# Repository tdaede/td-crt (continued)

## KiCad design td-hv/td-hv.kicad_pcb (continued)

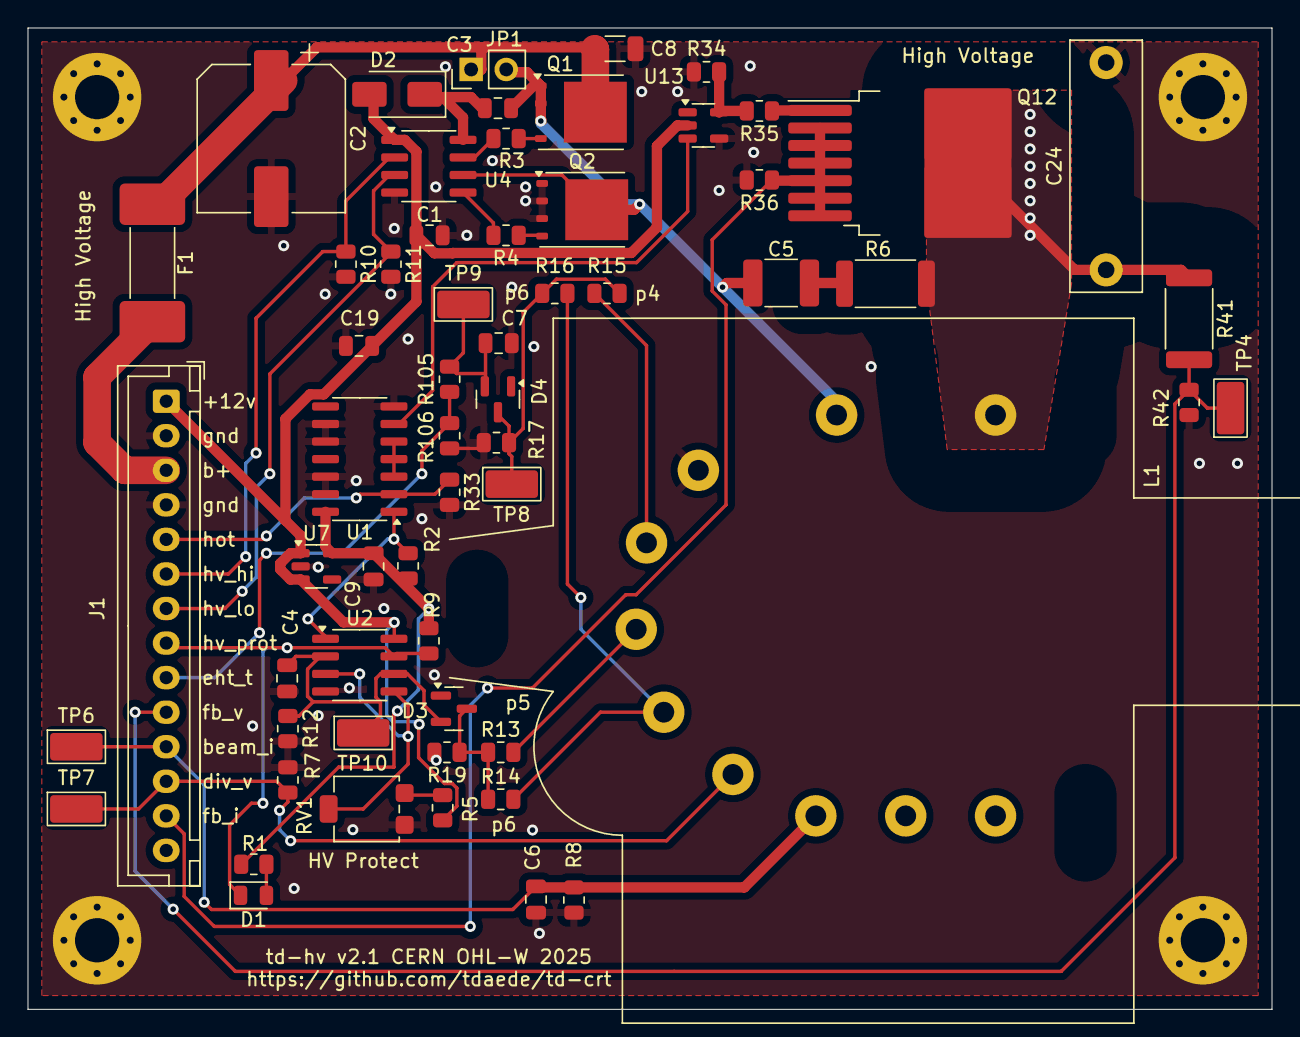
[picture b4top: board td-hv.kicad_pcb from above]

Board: 2 copper layers, 90.0 x 71.0 mm, 64 parts (0 on the bottom side), 37 nets.

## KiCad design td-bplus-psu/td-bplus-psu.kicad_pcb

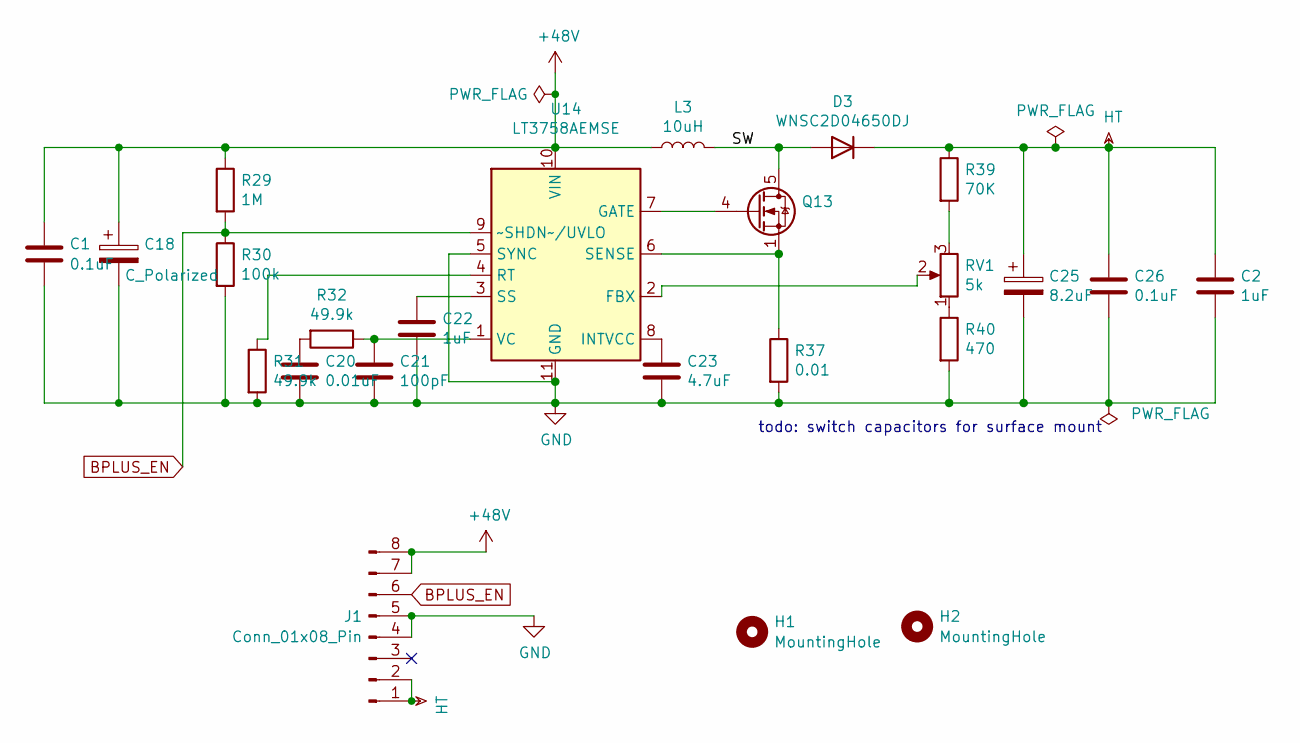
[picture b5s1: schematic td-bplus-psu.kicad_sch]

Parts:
C1: 0.1uF; C_0805_2012Metric; Digikey 399-C0805C104M5RAC7800CT-ND
C2: 1uF; C_2220_5750Metric_Pad1.97x5.40mm_HandSolder; Voltage 250V; Digikey 490-13318-1-ND
C18: C_Polarized; CP_Elec_6.3x5.9; Voltage 63V; Digikey P15466CT-ND
C20: 0.01uF; C_0805_2012Metric_Pad1.18x1.45mm_HandSolder; Voltage 10V; Digikey 1276-2434-1-ND
C21: 100pF; C_0805_2012Metric_Pad1.18x1.45mm_HandSolder; Voltage 10V; Digikey 1276-2569-1-ND
C22: 1uF; C_0805_2012Metric; Voltage 10V; Digikey 587-2229-1-ND
C23: 4.7uF; C_0805_2012Metric_Pad1.18x1.45mm_HandSolder; Voltage 10V; Digikey 1276-3177-1-ND
C25: 8.2uF; CP_Radial_D10.0mm_P5.00mm; Voltage 250V; Digikey 399-14135-ND
C26: 0.1uF; C_1206_3216Metric_Pad1.33x1.80mm_HandSolder; Voltage 250V; Digikey 311-4585-1-ND
D3: WNSC2D04650DJ; TO-252-2_TabPin1; Digikey 1740-WNSC2D04650DJCT-ND
H1, H2: MountingHole; MountingHole_2.7mm_M2.5
J1: Conn_01x08_Pin; PinHeader_1x08_P2.54mm_Horizontal
L3: 10uH; L_Wuerth_HCI-1040; Digikey 732-4179-1-ND
Q13: TDSON-8-1
R29: 1M; R_0805_2012Metric_Pad1.20x1.40mm_HandSolder; Digikey 311-1.00MCRCT-ND
R30: 100k; R_0805_2012Metric_Pad1.20x1.40mm_HandSolder; Digikey 311-100KCRCT-ND
R31, R32: 49.9k; R_0805_2012Metric_Pad1.20x1.40mm_HandSolder; Digikey 311-49.9KCRCT-ND
R37: 0.01; R_0805_2012Metric_Pad1.20x1.40mm_HandSolder; Digikey 311-0.01NUCT-ND
R39: 70K; R_1206_3216Metric_Pad1.30x1.75mm_HandSolder; Digikey 311-68.0KFRCT-ND
R40: 470; R_0805_2012Metric_Pad1.20x1.40mm_HandSolder; Digikey 311-470CRCT-ND
RV1: 5k; Potentiometer_Bourns_3314S_Horizontal; Digikey 3314S-1-502ECT-ND
U14: LT3758AEMSE; MSOP-10-1EP_3x3mm_P0.5mm_EP1.68x1.88mm; Digikey LT3758AEMSE#TRPBFCT-ND

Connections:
+48V: C1.1, C18.1, J1.7, J1.8, L3.1, R29.1, U14.10 (VIN)
/SW: D3.2 (A), L3.2, Q13.5 (D)
BPLUS_EN: J1.6, R29.2, R30.1, U14.9 (~SHDN~/UVLO)
GND: C1.2, C2.2, C18.2, C20.2, C21.2, C22.2, C23.2, C25.2, C26.2, J1.4, J1.5, R30.2, R31.2, R37.2, R40.2, U14.5 (SYNC), U14.11 (GND)
HT: C2.1, C25.1, C26.1, D3.1 (K), J1.1, J1.2, R39.1
unnamed: C20.1, R32.2
unnamed: Q13.4 (G), U14.7 (GATE)
unnamed: R39.2, RV1.3
unnamed: R40.1, RV1.1
unnamed: RV1.2, U14.2 (FBX)
unnamed: C23.1, U14.8 (INTVCC)
unnamed: R31.1, U14.4 (RT)
unnamed: Q13.1 (S), Q13.2 (S), Q13.3 (S), R37.1, U14.6 (SENSE)
unnamed: C22.1, U14.3 (SS)
unnamed: C21.1, R32.1, U14.1 (VC)

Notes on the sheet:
todo: switch capacitors for surface mount

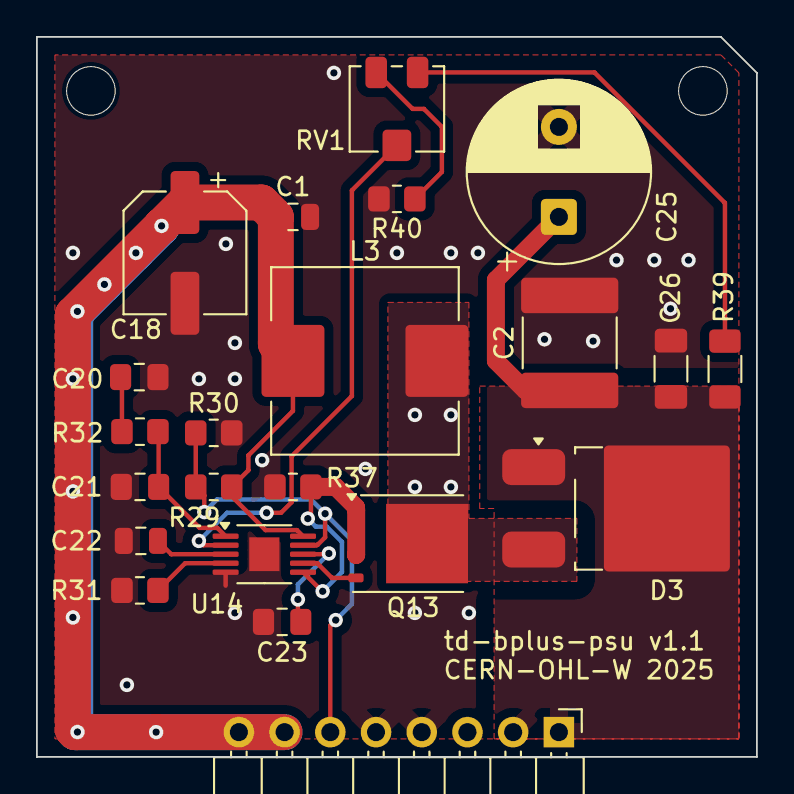
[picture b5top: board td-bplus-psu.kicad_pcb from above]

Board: 2 copper layers, 40.0 x 40.0 mm, 24 parts (0 on the bottom side), 15 nets.

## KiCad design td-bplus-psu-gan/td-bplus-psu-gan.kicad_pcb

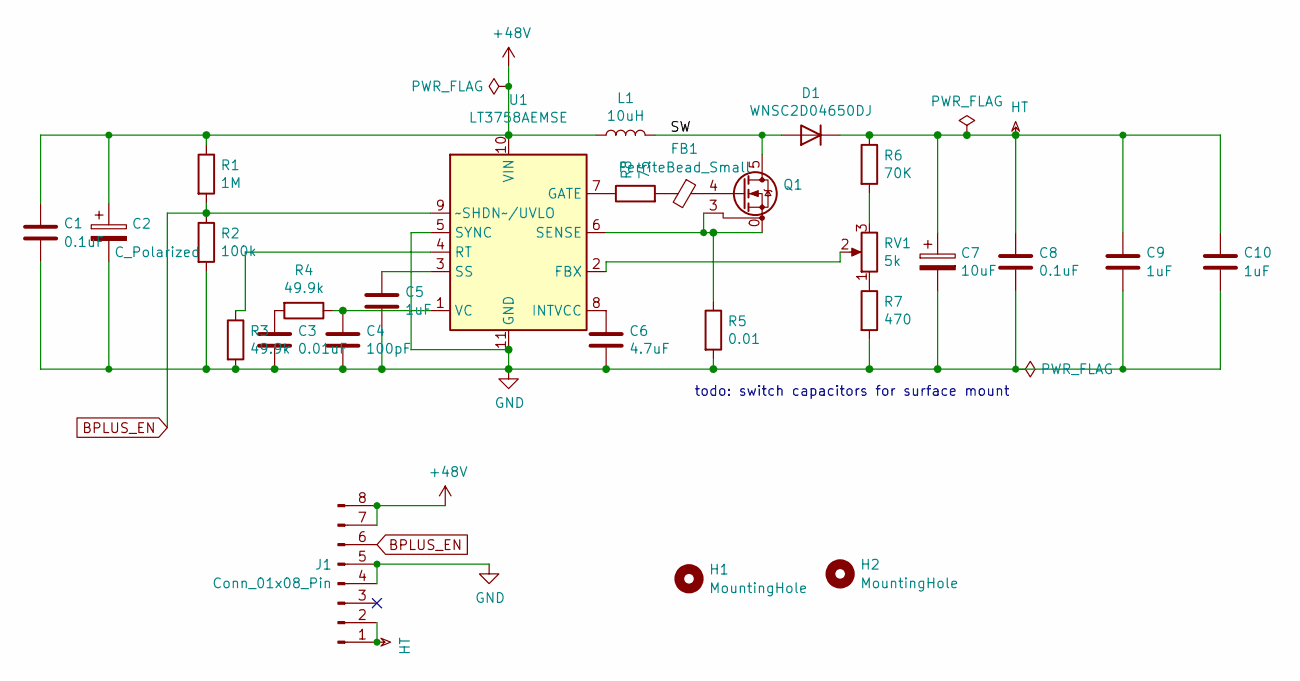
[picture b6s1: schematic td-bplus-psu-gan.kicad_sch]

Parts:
C1: 0.1uF; C_0805_2012Metric; Digikey 399-C0805C104M5RAC7800CT-ND
C2: C_Polarized; CP_Elec_6.3x5.9; Voltage 63V; Digikey P15466CT-ND
C3: 0.01uF; C_0805_2012Metric_Pad1.18x1.45mm_HandSolder; Voltage 10V; Digikey 1276-2434-1-ND
C4: 100pF; C_0805_2012Metric_Pad1.18x1.45mm_HandSolder; Voltage 10V; Digikey 1276-2569-1-ND
C5: 1uF; C_0805_2012Metric; Voltage 10V; Digikey 587-2229-1-ND
C6: 4.7uF; C_0805_2012Metric_Pad1.18x1.45mm_HandSolder; Voltage 10V; Digikey 1276-3177-1-ND
C7: 10uF; CP_Radial_D10.0mm_P5.00mm; Voltage 300V; Digikey 732-8889-1-ND
C8: 0.1uF; C_1206_3216Metric_Pad1.33x1.80mm_HandSolder; Voltage 250V; Digikey 311-4585-1-ND
C9, C10: 1uF; C_1812_4532Metric; Digikey 4713-CHV1812N250105KXTCT-ND
D1: WNSC2D04650DJ; TO-252-2_TabPin1; Digikey 1740-WNSC2D04650DJCT-ND
FB1: FerriteBead_Small; R_0603_1608Metric; Digikey 1712-BMC1JY0240ANCT-ND
H1, H2: MountingHole; MountingHole_2.7mm_M2.5
J1: Conn_01x08_Pin; PinHeader_1x08_P2.54mm_Horizontal; Digikey 609-3321-ND
L1: 10uH; L_Wuerth_HCI-1040; Digikey PCD2467CT-ND
Q1: Trasphorm_Power_DFN-8L_5x6; Digikey 1707-TP65H480G4JSGB-TRCT-ND
R1: 1M; R_0805_2012Metric_Pad1.20x1.40mm_HandSolder; Digikey 311-1.00MCRCT-ND
R2: 100k; R_0805_2012Metric_Pad1.20x1.40mm_HandSolder; Digikey 311-100KCRCT-ND
R3, R4: 49.9k; R_0805_2012Metric_Pad1.20x1.40mm_HandSolder; Digikey 311-49.9KCRCT-ND
R5: 0.01; R_0805_2012Metric_Pad1.20x1.40mm_HandSolder; Digikey 311-0.01NUCT-ND
R6: 70K; R_1206_3216Metric_Pad1.30x1.75mm_HandSolder; Digikey 311-68.0KFRCT-ND
R7: 470; R_0805_2012Metric_Pad1.20x1.40mm_HandSolder; Digikey 311-470CRCT-ND
R8: 75; R_0805_2012Metric; Digikey 311-75.0CRCT-ND
RV1: 5k; Potentiometer_Bourns_3314S_Horizontal; Digikey 3314S-1-502ECT-ND
U1: LT3758AEMSE; MSOP-10-1EP_3x3mm_P0.5mm_EP1.68x1.88mm; Digikey LT3758AEMSE#TRPBFCT-ND

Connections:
+48V: C1.1, C2.1, J1.7, J1.8, L1.1, R1.1, U1.10 (VIN)
/SW: D1.2 (A), L1.2, Q1.5 (D), Q1.6 (D), Q1.7 (D), Q1.8 (D)
BPLUS_EN: J1.6, R1.2, R2.1, U1.9 (~SHDN~/UVLO)
GND: C1.2, C2.2, C3.2, C4.2, C5.2, C6.2, C7.2, C8.2, C9.2, C10.2, J1.4, J1.5, R2.2, R3.2, R5.2, R7.2, U1.5 (SYNC), U1.11 (GND)
HT: C7.1, C8.1, C9.1, C10.1, D1.1 (K), J1.1, J1.2, R6.1
unnamed: C3.1, R4.2
unnamed: FB1.2, R8.2
unnamed: FB1.1, Q1.4 (G)
unnamed: Q1.0 (S), Q1.3 (KS), R5.1, U1.6 (SENSE)
unnamed: R6.2, RV1.3
unnamed: R7.1, RV1.1
unnamed: RV1.2, U1.2 (FBX)
unnamed: R8.1, U1.7 (GATE)
unnamed: C6.1, U1.8 (INTVCC)
unnamed: R3.1, U1.4 (RT)
unnamed: C5.1, U1.3 (SS)
unnamed: C4.1, R4.1, U1.1 (VC)

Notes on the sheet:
todo: switch capacitors for surface mount

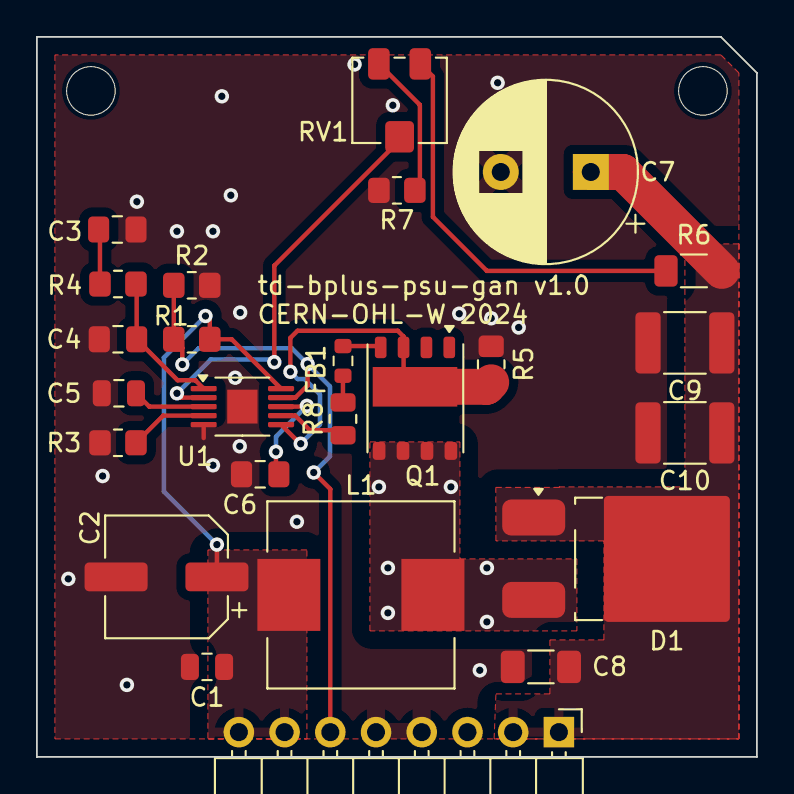
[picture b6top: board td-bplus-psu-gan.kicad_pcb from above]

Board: 2 copper layers, 40.0 x 40.0 mm, 27 parts (0 on the bottom side), 17 nets.

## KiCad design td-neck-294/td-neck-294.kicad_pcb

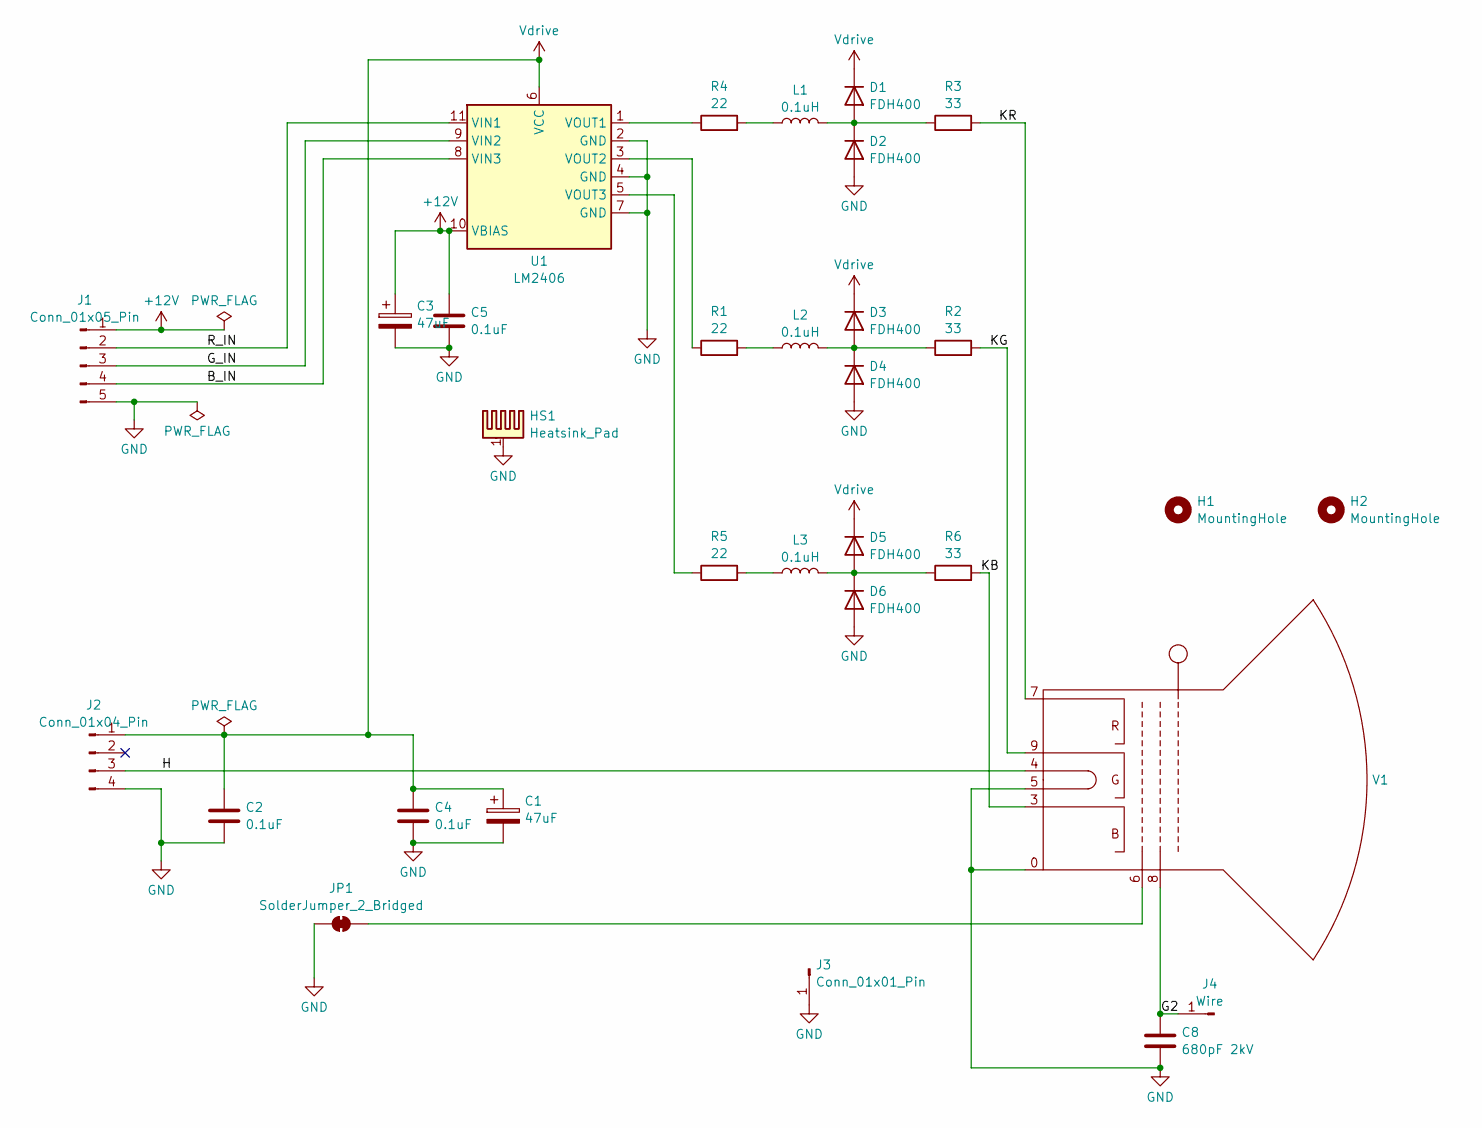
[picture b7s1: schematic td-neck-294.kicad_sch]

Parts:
C1, C3: 47uF; CP_Radial_D10.0mm_P5.00mm; Digikey 565-EKY-101ETD470MJC5SCT-ND
C2, C4, C5: 0.1uF; C_Disc_D8.0mm_W2.5mm_P5.00mm; Digikey BC1123CT-ND
C8: 680pF 2kV; C_Disc_D12.5mm_W5.0mm_P7.50mm; Digikey 445-CK45-B3FD681KYVNACT-ND
D1, D2, D3, D4, D5, D6: FDH400; D_DO-35_SOD27_P7.62mm_Horizontal_NoK; Digikey FDH400-ND
H1, H2: MountingHole; MountingHole_3.2mm_M3_ISO14580
HS1: Heatsink_Pad; Ohmite_RA-T2X-25E; Digikey RA-T2X-25E-ND
J1: Conn_01x05_Pin; JST_XH_B5B-XH-A_1x05_P2.50mm_Vertical; Digikey 455-B5B-XH-AM-ND
J2: Conn_01x04_Pin; JST_XH_B4B-XH-A_1x04_P2.50mm_Vertical; Digikey 455-B4B-XH-A-ND
J3: Conn_01x01_Pin; monitor_1p
J4: Wire; SolderWire-0.5sqmm_1x01_D0.9mm_OD2.3mm
JP1: SolderJumper_2_Bridged; SolderJumper-2_P1.3mm_Bridged_Pad1.0x1.5mm
L1, L2, L3: 0.1uH; L_Axial_L7.0mm_D3.3mm_P10.16mm_Horizontal_Fastron_MICC; Digikey M10147-ND
R1, R4, R5: 22; R_Axial_DIN0204_L3.6mm_D1.6mm_P5.08mm_Horizontal; Digikey S22CACT-ND
R2, R3, R6: 33; R_Axial_DIN0309_L9.0mm_D3.2mm_P12.70mm_Horizontal; Digikey 13-FKN-50JR-52-33RCT-ND
U1: LM2406; TO-220-11_P3.4x5.08mm_StaggerOdd_Lead4.85mm_Vertical
V1: GZS8-6-1

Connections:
+12V: C3.1, C5.1, J1.1, U1.10 (VBIAS)
/B_IN: J1.4, U1.8 (VIN3)
/G2: C8.1, J4.1, V1.8
/G_IN: J1.3, U1.9 (VIN2)
/H: J2.3, V1.4
/KB: R6.2, V1.3
/KG: R2.2, V1.9
/KR: R3.2, V1.7
/R_IN: J1.2, U1.11 (VIN1)
GND: C1.2, C2.2, C3.2, C4.2, C5.2, C8.2, D2.2 (A), D4.2 (A), D6.2 (A), HS1.1, J1.5, J2.4, J3.1, JP1.1 (A), U1.2 (GND), U1.4 (GND), U1.7 (GND), V1.0, V1.5
unnamed: D1.2 (A), D2.1 (K), L1.2, R3.1
unnamed: D3.2 (A), D4.1 (K), L2.2, R2.1
unnamed: D5.2 (A), D6.1 (K), L3.2, R6.1
unnamed: JP1.2 (B), V1.6
unnamed: L1.1, R4.2
unnamed: L2.1, R1.2
unnamed: L3.1, R5.2
unnamed: R4.1, U1.1 (VOUT1)
unnamed: R1.1, U1.3 (VOUT2)
unnamed: R5.1, U1.5 (VOUT3)
Vdrive: C1.1, C2.1, C4.1, D1.1 (K), D3.1 (K), D5.1 (K), J2.1, U1.6 (VCC)

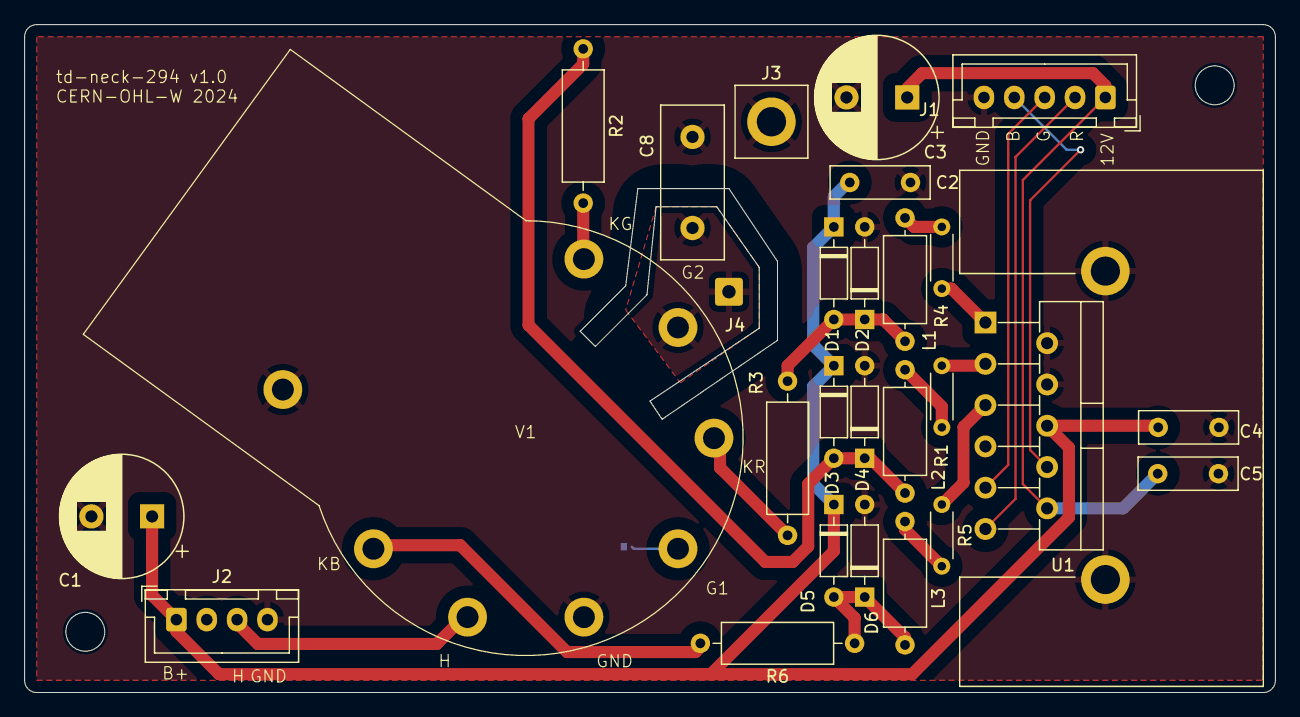
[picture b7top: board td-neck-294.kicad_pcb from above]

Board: 2 copper layers, 103.0 x 55.0 mm, 31 parts (1 on the bottom side), 21 nets.

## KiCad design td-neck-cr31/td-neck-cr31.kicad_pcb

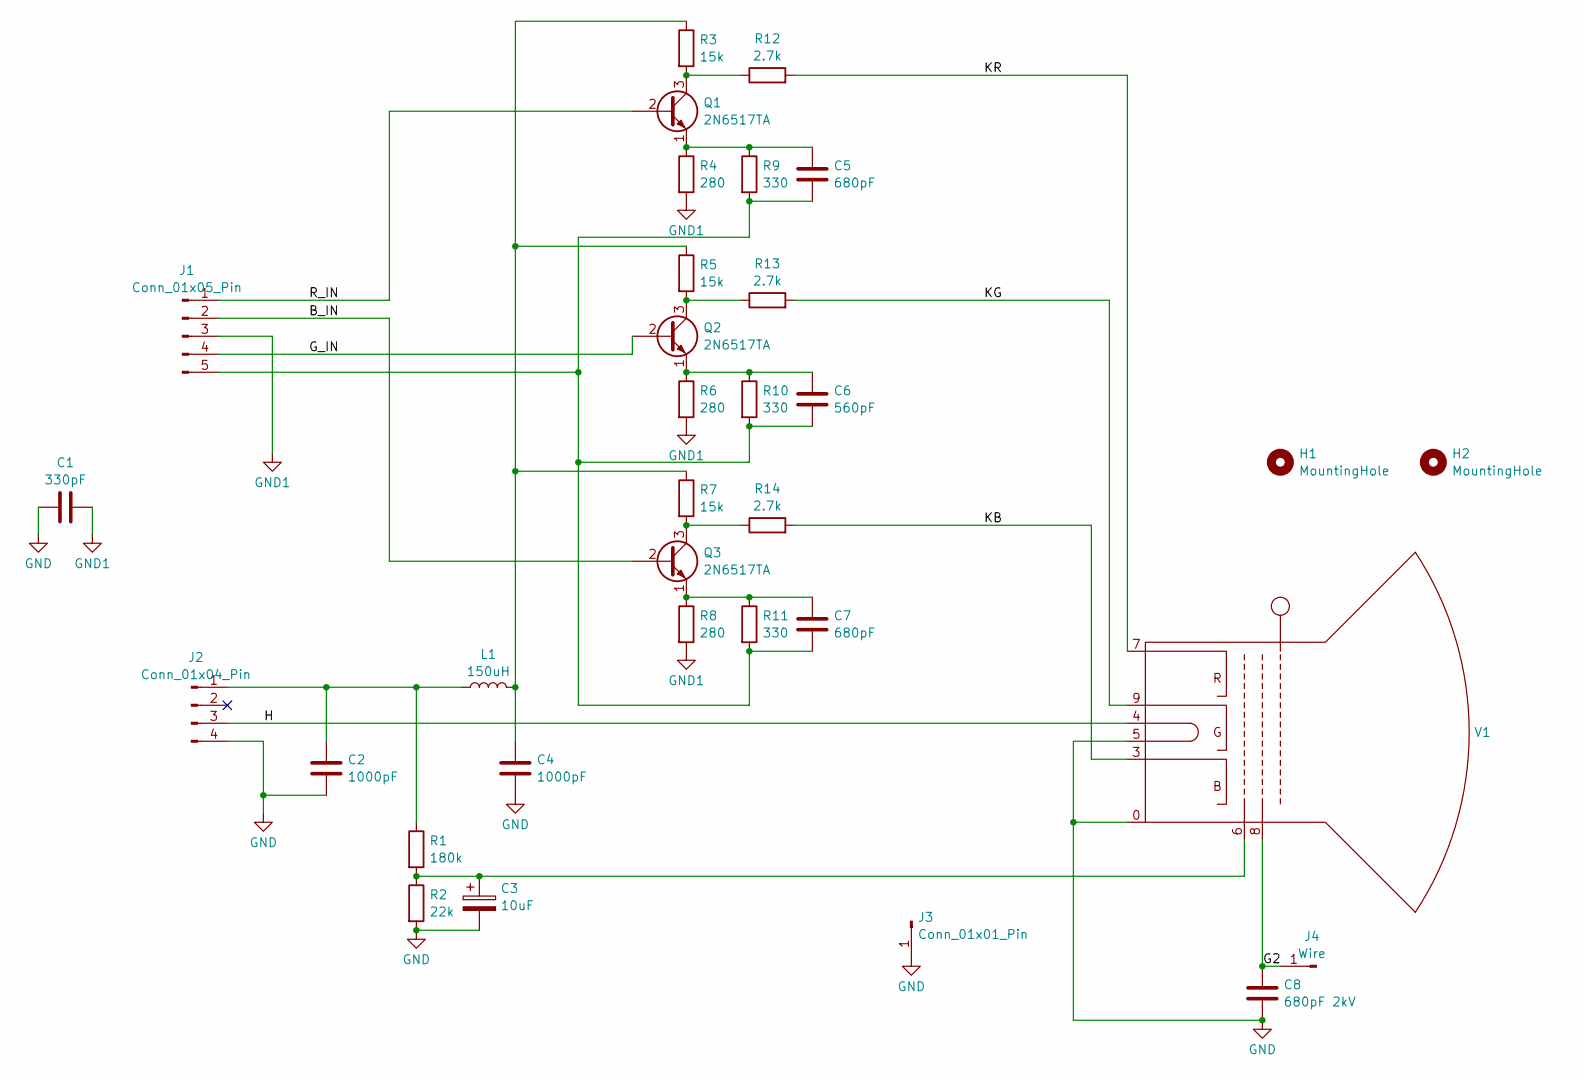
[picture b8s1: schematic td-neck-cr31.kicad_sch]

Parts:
C1: 330pF; C_Disc_D5.0mm_W2.5mm_P5.00mm; Digikey 445-180761-1-ND
C2, C4: 1000pF; C_Disc_D8.0mm_W2.5mm_P5.00mm; Digikey 445-180754-1-ND
C3: 10uF; CP_Radial_D6.3mm_P2.50mm; Digikey 399-6094-ND
C5, C7: 680pF; C_Disc_D5.0mm_W2.5mm_P5.00mm; Digikey 445-180765-1-ND
C6: 560pF; C_Disc_D5.0mm_W2.5mm_P5.00mm; Digikey 445-180765-1-ND
C8: 680pF 2kV; C_Disc_D12.5mm_W5.0mm_P7.50mm; Digikey 445-CK45-B3FD681KYVNACT-ND
H1, H2: MountingHole; MountingHole_3.2mm_M3_ISO14580
J1: Conn_01x05_Pin; JST_XH_B5B-XH-A_1x05_P2.50mm_Vertical; Digikey 455-B5B-XH-AM-ND
J2: Conn_01x04_Pin; JST_XH_B4B-XH-A_1x04_P2.50mm_Vertical; Digikey 455-B4B-XH-A-ND
J3: Conn_01x01_Pin; monitor_1p
J4: Wire; SolderWire-0.5sqmm_1x01_D0.9mm_OD2.3mm
L1: 150uH; L_Axial_L5.3mm_D2.2mm_P7.62mm_Horizontal_Vishay_IM-1; Digikey 118-78F151J-RC-ND
Q1, Q2, Q3: 2N6517TA; TO-92_Wide; Digikey 2N6517TACT-ND
R1: 180k; R_Axial_DIN0204_L3.6mm_D1.6mm_P5.08mm_Horizontal; Digikey S180KQCT-ND
R2: 22k; R_Axial_DIN0204_L3.6mm_D1.6mm_P5.08mm_Horizontal; Digikey S22KQCT-ND
R3, R5, R7: 15k; R_Axial_DIN0309_L9.0mm_D3.2mm_P12.70mm_Horizontal; Digikey A138268CT-ND
R4, R6, R8: 280; R_Axial_DIN0204_L3.6mm_D1.6mm_P5.08mm_Horizontal; Digikey S270QCT-ND
R9, R10, R11: 330; R_Axial_DIN0204_L3.6mm_D1.6mm_P5.08mm_Horizontal; Digikey S330QCT-ND
R12, R13, R14: 2.7k; R_Axial_DIN0207_L6.3mm_D2.5mm_P10.16mm_Horizontal; Digikey S2.7KHCT-ND
V1: GZS8-6-1

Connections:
/B_IN: J1.2, Q3.2 (B)
/G2: C8.1, J4.1, V1.8
/G_IN: J1.4, Q2.2 (B)
/H: J2.3, V1.4
/KB: R14.2, V1.3
/KG: R13.2, V1.9
/KR: R12.2, V1.7
/R_IN: J1.1, Q1.2 (B)
GND: C1.1, C2.2, C3.2, C4.2, C8.2, J2.4, J3.1, R2.2, V1.0, V1.5
GND1: C1.2, J1.3, R4.2, R6.2, R8.2
unnamed: C3.1, R1.2, R2.1, V1.6
unnamed: C4.1, L1.2, R3.1, R5.1, R7.1
unnamed: C5.2, C6.2, C7.2, J1.5, R9.2, R10.2, R11.2
unnamed: C2.1, J2.1, L1.1, R1.1
unnamed: Q1.3 (C), R3.2, R12.1
unnamed: C5.1, Q1.1 (E), R4.1, R9.1
unnamed: Q2.3 (C), R5.2, R13.1
unnamed: C6.1, Q2.1 (E), R6.1, R10.1
unnamed: Q3.3 (C), R7.2, R14.1
unnamed: C7.1, Q3.1 (E), R8.1, R11.1

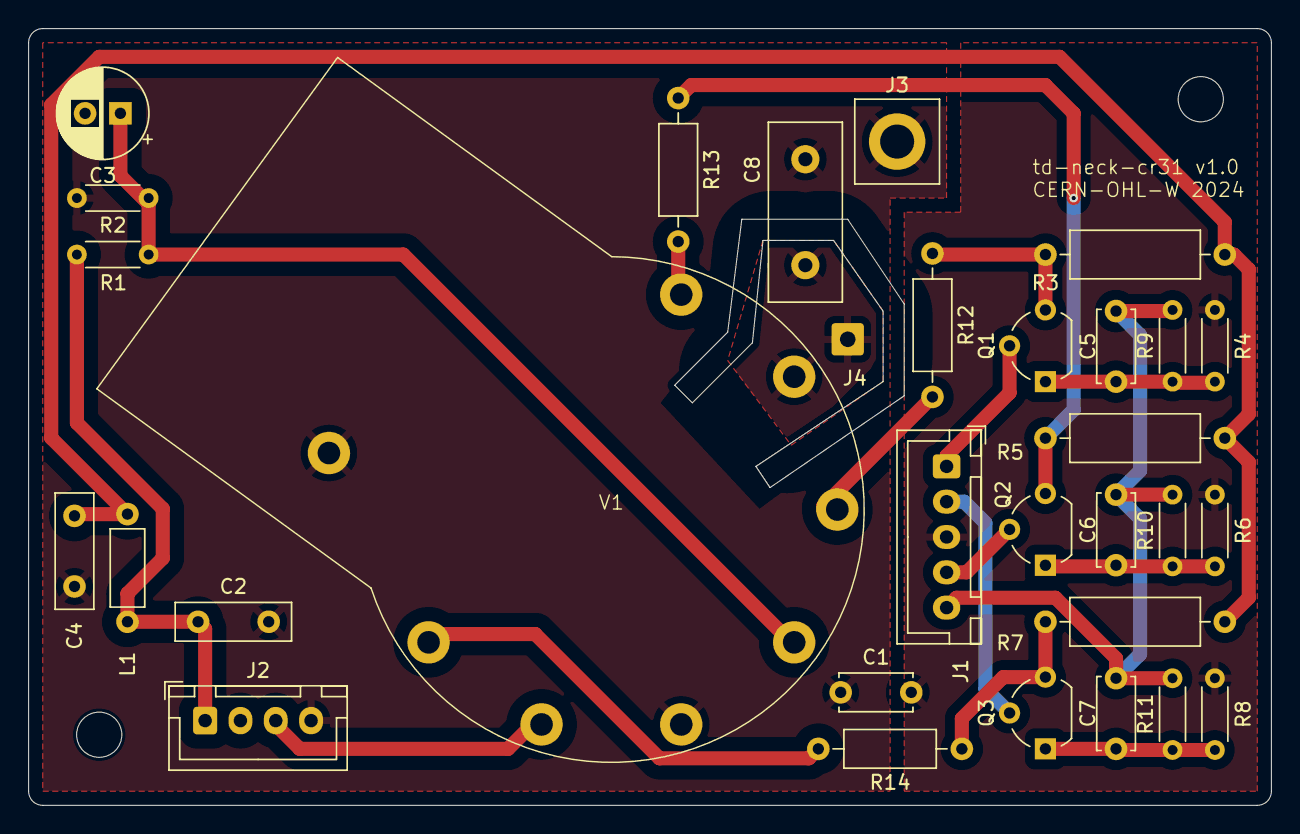
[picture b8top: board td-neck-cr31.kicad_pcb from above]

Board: 2 copper layers, 88.0 x 55.0 mm, 33 parts (0 on the bottom side), 20 nets.

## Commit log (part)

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2018-12-23 add td-rgb
2018-12-27 I have no idea what I'm doing
2018-12-27 td-rgb 1.0
2019-01-27 various updates
2019-01-27 add 1.0 gerbers
2019-01-27 Add 3d printed bracket
2019-02-07 Update footprint for DE-15 connector to correct pin row spacing
2019-02-07 Correct DE-15 placement on PCB to bring closer to original design
2019-08-08 add firmware
2019-10-08 drop some of the old GaNs
2019-10-09 Add power supplies
2019-10-09 drop LM5022 boost
2019-10-10 Update firmware to not use a git version of hal
2019-10-27 add lots of stuff
2019-10-27 annotate
2019-10-28 more stuff
2019-11-20 asdf
2019-12-03 Fix some part #s
2019-12-03 Fix vertical deflection output wiring
2020-01-18 uart
2021-06-22 Add 180v psu
2021-07-06 180v fixes
2021-07-06 more fixes
2021-07-25 add td-hv
2021-07-26 hv schematic
2021-07-26 footprints
2021-07-26 add digikey pns
2021-07-29 Add default cargo target for firmware
2021-08-01 stuff
2021-08-01 add gui
2021-08-01 it werks
2021-08-01 add flash script
2021-08-02 add vertical maths
2021-08-02 Drop num_traits in favor of builtin clamp type
2021-08-02 Bump to rtic 0.5.5
2021-08-02 Update stm32f7 crate
2021-08-02 update stm32f7xx-hal
2021-08-03 Add JSON stats output.
2021-08-03 drop HAL for now
2021-08-03 Add serial support to gui
2021-08-03 bump serde
2021-08-04 add input and output period
2021-08-05 lots of stuff
2021-08-05 remove panic_halt
2021-08-05 fix comments
2021-08-06 Switch to composite sync VSYNC
2021-08-13 some td-hv layout
2021-08-14 add output for vertical ssr
2021-08-14 update firmware deps
2021-08-14 update gui deps
2021-08-14 fix warning in gui
2021-08-15 temporary fix for bad bootstrap diode
2021-08-15 allow control of crt stats via computer
2021-08-15 Add serial send queue
2021-08-16 make gui sending work
2021-08-16 add vertical offset
2021-08-16 add hsize slider
2021-08-17 Add library cache
2021-08-17 Add rescue library for td-deflect
2021-08-17 Convert schematic to newer nightly format
2021-08-17 convert deflect pcb to newer nightly
2021-08-17 add todos to schematic
2021-08-20 Add new deadzone for 75 ohm gate resistors
2021-08-21 synchronize hpin to input
2021-08-22 implement phase error averaging
2021-08-22 Synchronize h pin in software
2021-08-22 add unused code to run interrupts from ram
2021-08-23 Move stack to DTCM
2021-08-24 don't sync during visible scan
2021-08-24 Double TIM3 clock rate
2021-08-25 switch HOT to use TIM1 CH4
2021-08-26 Add hardware phase error capture
2021-08-26 remove unnecessary unsafe blocks
2021-08-26 update deps
2021-08-26 use newer cortex-m crate
2021-08-26 drop semihosting
2021-08-26 tell rtic to use cortex-m 0.7.x
2021-08-26 tweak feedback gain
2021-08-26 add super basic vertical linearity correction
2021-08-27 better linearity approximation
2021-08-28 make vertical linearity part of the config
2021-08-31 Add vertical linearity to gui
2021-08-31 Add error diffusion for vertical drive
2021-08-31 add error diffusion to h period
2021-09-07 more td-hv layout
2021-09-07 update td-rgbinput
2021-09-13 pn updates for hv
2021-09-13 use software triggering for vertical output
2021-09-18 Add S-cap adjust
2021-09-18 add InputConfig
2021-09-19 update some gui deps
2021-09-19 add input configuration sending
2021-09-19 add h.size
2021-09-19 fix a few lints
2021-09-19 use much faster deque for serial sending
2021-09-19 use rtic message passing to send stats
2021-09-19 remove dead code
2021-09-19 add h phase adjust
2021-09-20 fix CRT stats clearing per field
2021-09-20 interlacing support
2021-09-20 correct field naming
2021-09-25 td-hv bugfixes
2021-10-04 Add .pdf exports of some schematics
2021-10-21 more rgbinput changes
2021-10-31 td-rgbinput
2021-11-03 td-hv improvements
2021-11-30 add real readme
2021-12-01 use links in readme
2021-12-01 Add 180v readme
2021-12-01 add rgbinput readme
2021-12-01 add td-hv readme
2021-12-01 add deflection README
2021-12-11 add missing sch file
2021-12-13 add todos
2021-12-18 update td-rgbinput to kicad 6.0.0-rc2
2021-12-18 fix todos
2021-12-19 finish pcb
2021-12-19 fill a few extra areas
2021-12-19 fix zones
2021-12-19 update footprints from kicad 6 library
2021-12-19 increment version number
2021-12-19 remove old format schematic
2021-12-19 convert td-hv to kicad 6
2021-12-23 finish layout
2021-12-29 add missing file for td-hv
2021-12-30 add missing td-180v file
2021-12-30 update td-hv schematic to match currently built circuit
2021-12-30 attach vcc to the 3845
2021-12-30 change part number of ucc38c45
2021-12-30 switch tlc272 power source to 5v
2022-02-14 update td-rgbinput to reflect constructed circuit
2022-06-06 Bump regex from 1.5.4 to 1.5.6 in /td-deflect/td-deflect-gui
    Bumps [regex](https://github.com/rust-lang/regex) from 1.5.4 to 1.5.6.
    - [Release notes](https://github.com/rust-lang/regex/releases)
    - [Changelog](https://github.com/rust-lang/regex/blob/master/CHANGELOG.md)
    - [Commits](https://github.com/rust-lang/regex/compare/1.5.4...1.5.6)
    ---
    updated-dependencies:
2022-12-10 Autoselect usb to serial converter
2022-12-19 update fp-info-cache
2022-12-19 add HV driver to software
2022-12-23 random td-rgbinput changes
2022-12-23 update td-deflect kicad version
2022-12-23 update some transistors, remove current sense amp
2022-12-25 new vertical amp
2022-12-26 update vertical
2022-12-26 switch to newer sic mosfet
2022-12-26 replace S capacitors
2022-12-26 remove recirculating schottky diode
2022-12-26 add gate resistors to top drive
2022-12-26 switch b+ diode to sic
2022-12-27 switch ti to rohm switching power ic
2022-12-27 replace negative supply with coupled inductor
2022-12-28 add switching heater supply
2022-12-28 switch to stm32g4
2022-12-28 current measurement for h
2022-12-28 make bootstrap circuit not bootstrap as much
2023-01-02 add class d vertical amp
2023-01-02 switch to smt hot
2023-01-03 switch to new sic for hv
2023-01-03 more hv stuff
2023-01-03 special hv resistor
2023-01-03 add hv protect and more sense lines
2023-01-04 add connector for power
2023-01-04 add degauss circuit
2023-01-08 Update td-deflect-gui deps
2023-01-24 add faulted atomic boolean
2023-01-24 add basic vertical blanking
2023-01-25 connect more uc pins
2023-01-25 convert schematic to kicad 7 format
2023-01-25 switch to kicad official uc symbol
2023-02-13 Add LM1205 symbol
2023-03-24 initial commit of book
2023-03-24 Add regulation section
2023-04-24 update kicad format and move flyback to separate sheet
2023-04-24 Add independent cathode supply
2023-09-20 add murata footprint
2023-09-20 drop current sense note
2023-09-20 more updates
2023-09-20 modify flyback feedback mechanism
2023-09-20 add separate analog power supply
2023-09-21 even more updates
2023-09-21 small bugfix
2023-09-21 bump gui lock file
2023-09-22 new version of td-hv, microcontroller control only
2023-09-22 switch to new 0805 footprint
2023-09-23 Update to newer serde-json-core
2023-09-23 Move CRT protocol definition to separate crate
2023-09-24 remove debug code
2023-09-24 td-hv 2.0 changes
2023-09-25 small bom changes
2023-09-30 Add td-rgbinput-lm1205
2023-10-04 add td-hv todo
2023-10-04 add rgbinput-remote
2023-10-04 add kicad_prl to gitignore
2023-10-07 add fp-info-cache to gitignore
2023-10-07 small lm1205 fixup
2023-10-07 split off adc into its own file
2023-10-07 move adc gpio initialization into adc file
2023-10-07 move adc rcc init into adc.rs
2023-10-07 split serial into serial.rs
2023-10-07 move serial gpio/rcc init to serial module
2023-10-08 add split rail psu
2023-10-08 update gitignore
2023-10-20 update bplus psu
2023-11-27 bplus
2023-11-27 split-rail-psu
2023-11-27 finish split rail psu pcb
2023-11-27 switch to 100 pin tqfp microcontroller
2023-11-27 use off board bplus h supply
2023-11-27 use off board f and c supply
2023-11-27 use off board +12/-12/+6v supplies
2023-11-27 use offboard flyback
2023-11-27 update part numbers
2023-11-27 external rgb
2023-11-28 update some symbols
2023-11-29 fix drc errors
2023-11-29 fix remaining erc errors
2023-11-29 assign more footprints
2023-12-04 more layout work
2023-12-19 more layout
2024-01-23 update pcb
2024-01-26 remove bad digikey pn
2024-02-18 final td-deflect 0.2 changes
2024-02-19 initial conversion to stm32g4
2024-02-19 add todo notes
2024-02-19 Update to new brr register in stm32-rs
2024-02-20 enable vertical dac
2024-02-20 actually enable the dac
2024-02-21 enable hot output via tim1
2024-02-21 add h width and s caps
2024-02-22 enable hv pwm output
2024-02-22 double apb clocks
2024-02-22 enable adc
2024-02-22 use recommended clock speed increase method
2024-02-22 run at 170mhz
2024-02-22 add class d driver
2024-02-23 enable horizontal sync
2024-02-23 enable vsync input
2024-02-23 support both sync inputs
2024-02-24 fix some more gpios
2024-02-26 open loop vertical model
2024-03-02 add some notes
2024-03-02 ignore serial overruns
2024-03-02 convert serial to fifo mode the lazy way
2024-03-02 update gui to edition 2021
2024-03-02 convert gui stats channel to async-channel
2024-03-02 fix system clock in gui
2024-03-02 reduce vertical dead time
2024-03-03 add initial vertical scope
2024-03-03 use oversampling for adc
2024-03-03 up serial baud rate
2024-03-03 switch to adc2 for vertical current
2024-03-12 Add neck board
2024-03-13 round corners
2024-03-15 adjust pcb text
2024-03-15 Add basic scan fault detector for vertical.
2024-04-05 modify for new mosfets
2024-04-27 small config changes
2024-06-03 add 294 neck board
2024-06-03 add bplus psu gan
2024-06-19 grup bplus psu gan bom
2024-08-01 add missing gui scope files
2024-09-30 Update to newest stm32-rs nightly
2024-09-30 rename cargo config to config.toml
2024-09-30 Migrate to rtic2
    this temporarily loses interrupt execution from ram support
2024-10-01 fix occasional status message corruption
2024-10-01 update gui dependencies
2024-10-01 update async-channel
2024-10-04 switch tx to bounded queue to avoid lag
2024-10-04 move HOT drive to a separate file
2025-07-13 Update td-rgbinput-lm1205 to add decoupling caps etc
2025-07-13 update td-hv to new format
2025-07-13 do some basic fixes
2025-07-13 update td-hv cache
2025-07-13 Remove class AB vertical deflection circuit
2025-07-13 swap to recom modules for 3.3V rails
2025-08-28 shrink board a lot
2025-09-12 add realistic config
2025-09-14 update gui to match realistic tv default values
2025-10-03 finish board
2025-10-03 Update bplus psu to have better caps and pot facing the right dir
2025-10-03 Generate output for td-rgbinput-lm1205 v1.1
2025-10-03 Adjust td-hv pin spacing and add a bypass jumper
2025-10-10 Update bplus psu for better caps
2025-10-10 update td-hv bom
2025-10-10 update td-rgbinput-lm1205 bom
2025-10-10 update rgbinput remote bom
2025-11-06 update firmware for nec tv
2026-01-04 adjust for nec monitor slightly
2026-01-04 set time to 1/2
2026-01-22 more hacks
2026-01-22 small pcb change
2026-01-22 fix some small td-hv issues
2026-01-22 swap to cheaper sic mosfet
2026-01-22 swap to cheaper capacitor
2026-02-09 Update td-rgbinput-lm1205 to add a linear regulator.
2026-02-09 Add new rgb / geometry combined remote
2026-06-11 bunch of random updates
